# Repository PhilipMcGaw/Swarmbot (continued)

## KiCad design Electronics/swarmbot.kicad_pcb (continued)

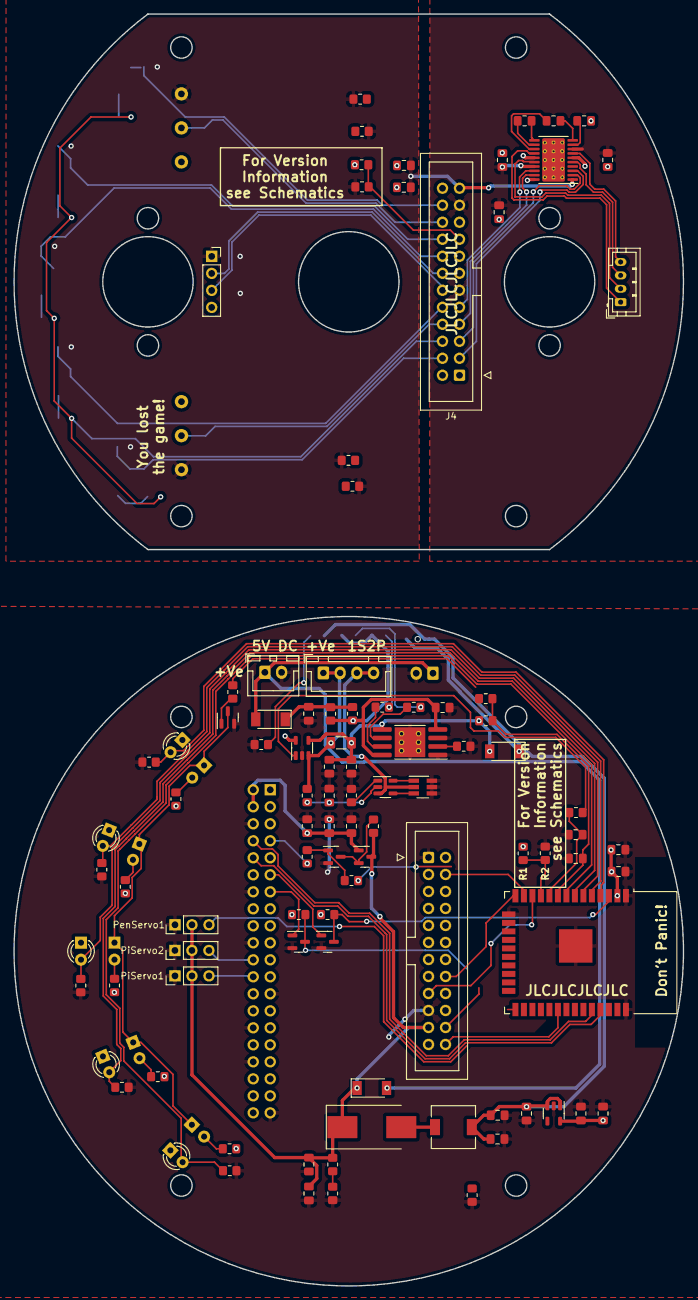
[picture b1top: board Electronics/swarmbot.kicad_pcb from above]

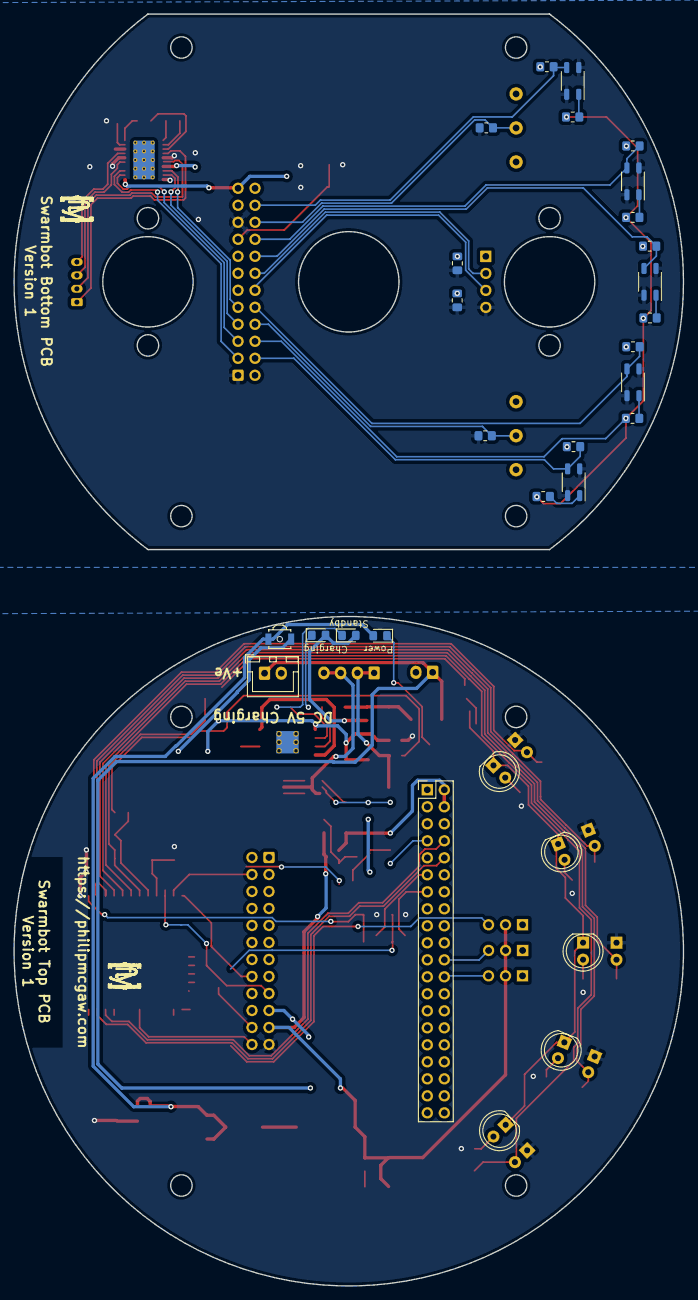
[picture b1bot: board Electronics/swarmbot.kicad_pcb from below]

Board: 2 copper layers, 100.0 x 190.0 mm, 131 parts (32 on the bottom side), 105 nets.

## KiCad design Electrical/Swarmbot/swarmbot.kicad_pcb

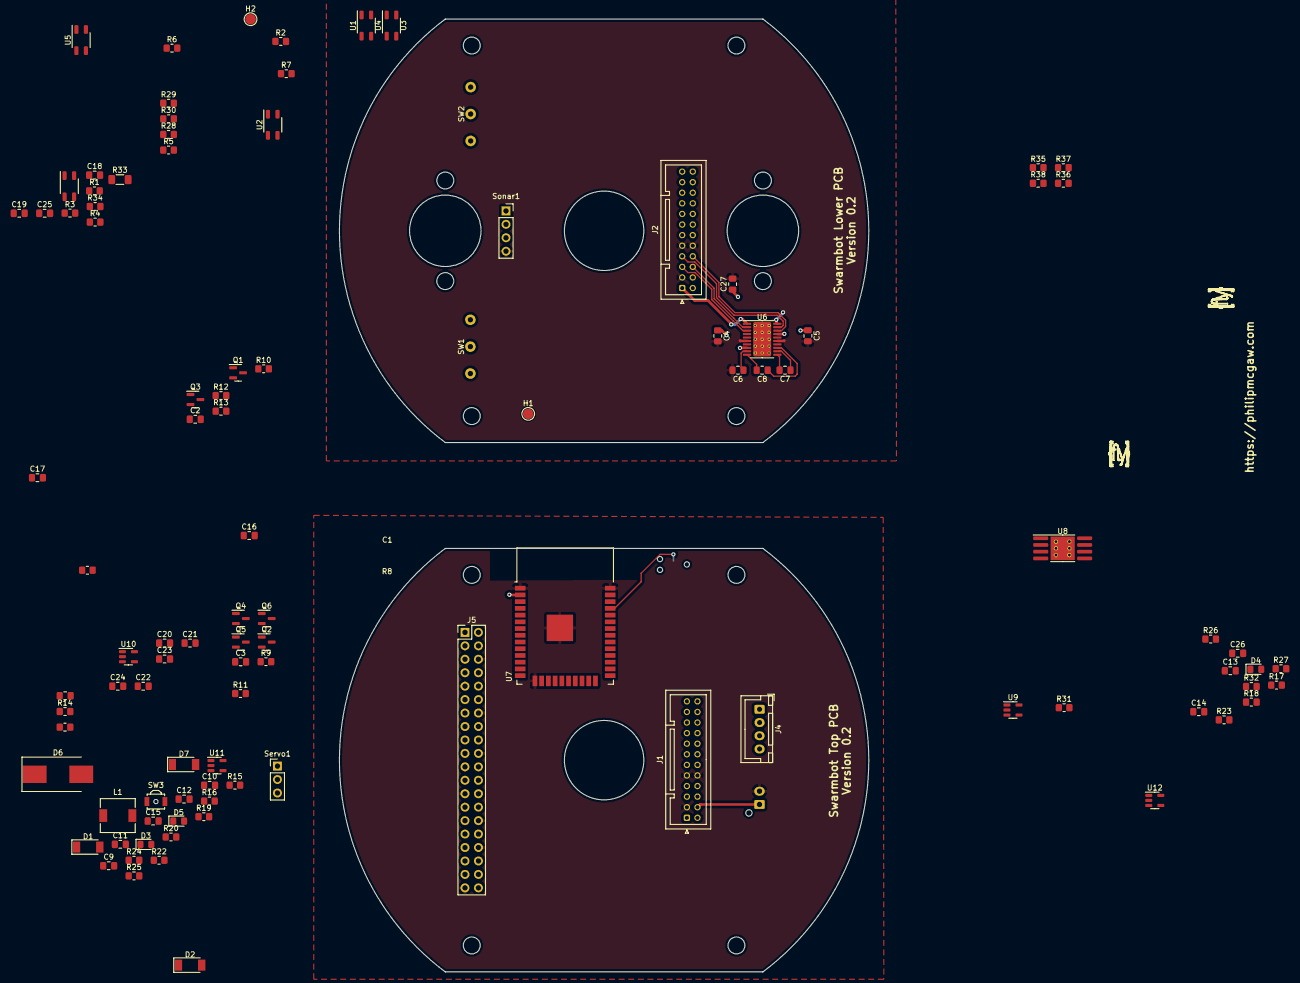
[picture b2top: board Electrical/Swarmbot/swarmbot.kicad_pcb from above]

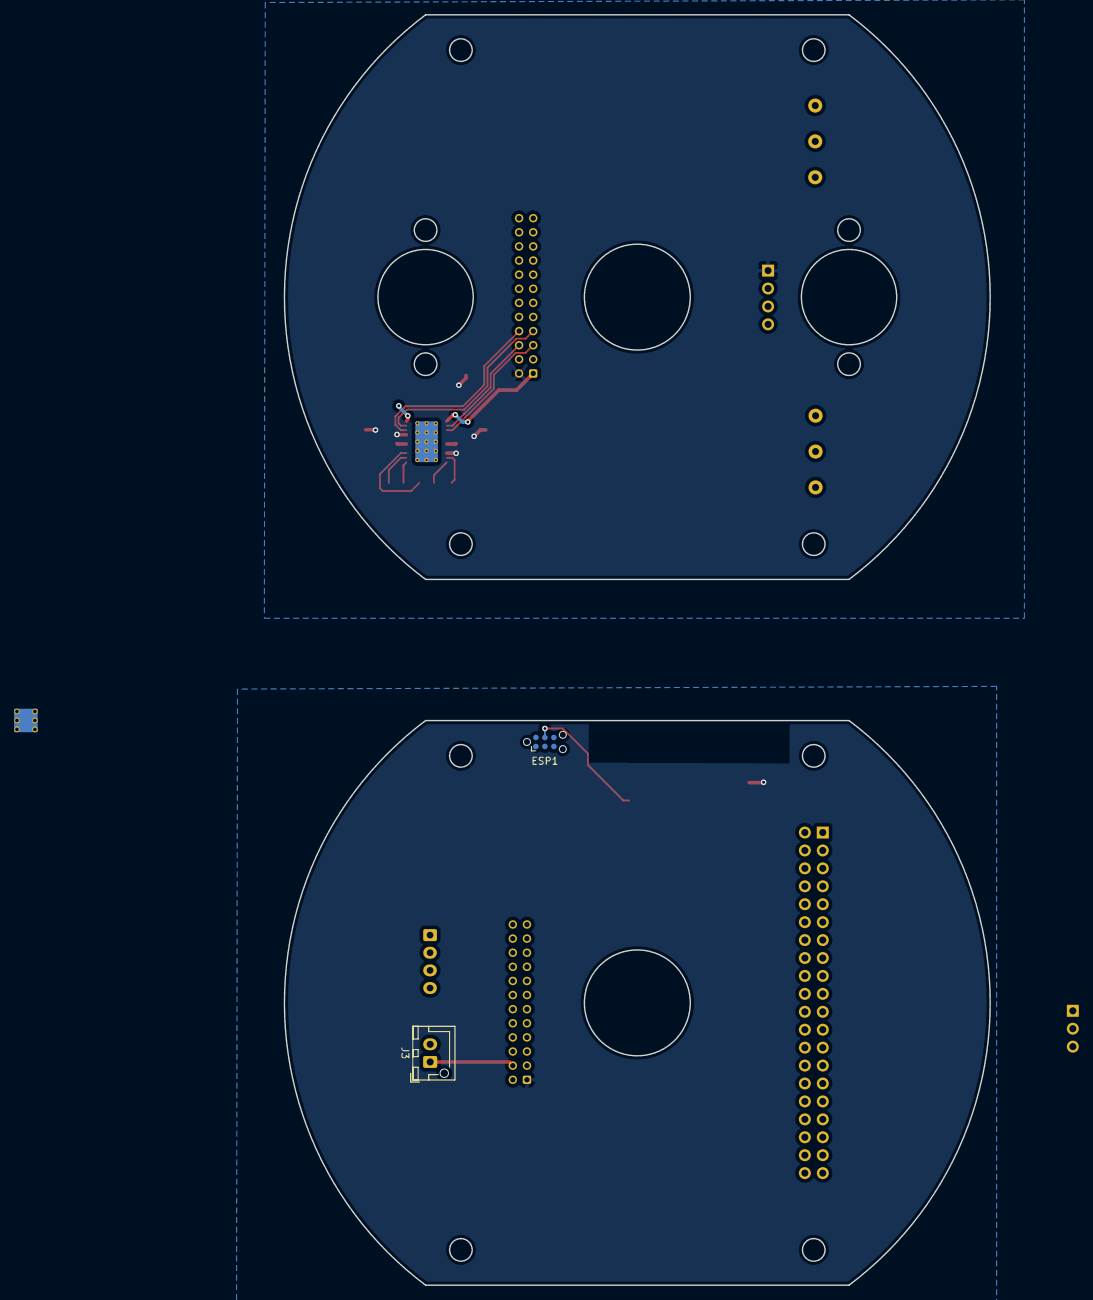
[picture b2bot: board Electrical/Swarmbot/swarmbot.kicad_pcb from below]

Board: 2 copper layers, 100.0 x 180.0 mm, 106 parts (2 on the bottom side), 84 nets.

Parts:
C1, C2, C9, C10, C11, C13, C14, C17, C22, C25: 10uF; C_0805_2012Metric_Pad1.18x1.45mm_HandSolder
C3, C4, C5, C6, C7, C8, C12, C26, C27: 100pF; C_0805_2012Metric_Pad1.18x1.45mm_HandSolder
C15, C16, C19, C20: 22uF; C_0805_2012Metric_Pad1.18x1.45mm_HandSolder
C18, C24: 100nF; C_0805_2012Metric_Pad1.18x1.45mm_HandSolder
C21, C23: 1uF; C_0805_2012Metric_Pad1.18x1.45mm_HandSolder
D1, D2, D7: RBR3LAM30BTFTR; D_SOD-128
D3: Power; LED_0805_2012Metric_Pad1.15x1.40mm_HandSolder
D4: Charging; LED_0805_2012Metric_Pad1.15x1.40mm_HandSolder
D5: Standby; LED_0805_2012Metric_Pad1.15x1.40mm_HandSolder
D6: SS54; D_SMC_Handsoldering
ESP1: ESP Programming TagConnect; Tag-Connect_TC2030-IDC-NL_2x03_P1.27mm_Vertical
H1: +VE; TestPoint_Pad_D2.0mm
H2: -VE; TestPoint_Pad_D2.0mm
J1, J2: 12x2 JST; JST_PUD_B24B-PUDSS_2x12_P2.00mm_Vertical
J3: Charging Header; JST_XH_B2B-XH-AM_1x02_P2.50mm_Vertical
J4: Battery 1S2P; JST_XH_B4B-XH-A_1x04_P2.50mm_Vertical
J5: Raspberry_Pi_2_3; PinHeader_2x20_P2.54mm_Vertical
L1: 3.3uH; L_6.3x6.3_H3
Logo1, Logo2: SquashedFlyLogo; SquashedFlySilk
Q1, Q2, Q3, Q4: BSH108; SOT-23
Q5, Q6: RSC002P03; SOT-23
R1, R2, R8, R9, R10, R11, R12, R13, R14, R15, R16, R17, R18, R19, R20, R21, R30, R37, R38: 10k; R_0805_2012Metric_Pad1.20x1.40mm_HandSolder
R3, R4, R5, R6, R7, R35, R36: 470; R_0805_2012Metric_Pad1.20x1.40mm_HandSolder
R22, R25, R26: 1k; R_0805_2012Metric_Pad1.20x1.40mm_HandSolder
R23, R24: 2R; R_0805_2012Metric_Pad1.20x1.40mm_HandSolder
R27: 30k; R_0805_2012Metric_Pad1.20x1.40mm_HandSolder
R28: 1k2; R_0805_2012Metric_Pad1.20x1.40mm_HandSolder
R29: 73k; R_0805_2012Metric_Pad1.20x1.40mm_HandSolder
R31, R34: 2k7; R_0805_2012Metric_Pad1.20x1.40mm_HandSolder
R32: 330; R_0805_2012Metric_Pad1.20x1.40mm_HandSolder
R33: .0025R; R_1206_3216Metric_Pad1.30x1.75mm_HandSolder
SW1: Left; TypeD
SW2: Right; TypeC
SW3: SW_SPST; SW_SPST_B3U-3000P-B
Servo1: Conn_01x03_Male; PinHeader_1x03_P2.54mm_Vertical
Sonar1: Conn_01x04_Male; PinSocket_1x04_P2.54mm_Vertical
U1, U2, U3, U4, U5: QRE1113GR; OnSemi_CASE100CY
U6: MPC17531A; HTSSOP-20-1EP_4.4x6.5mm_P0.65mm_EP3.4x6.5mm_Mask2.75x3.43mm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
U7: ESP32-WROOM-32D; ESP32-WROOM-32
U8: TP4056; SOP-8-1EP_4.57x4.57mm_P1.27mm_EP4.57x4.45mm_ThermalVias
U9, U11: AP2112K-3.3; SOT-23-5
U10: AP9101CK; SOT-23-5
U12: INA138; SOT-23-5

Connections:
+3V3: C11.1, C12.1, C22.1, C23.1, ESP1.1 (VCC), J1.1, R16.1, R17.1, U7.2 (VDD), U9.5 (VOUT), U11.5 (VOUT), U12.5 (V+)
+5V: C19.1, C20.1, D6.1 (K), D7.1 (K), J1.2, Q5.3 (D), Q6.3 (D), R18.1, R19.1, R29.2, Servo1.2
+BATT: C17.1, C18.1, D1.2 (A), R20.2, R32.2, R33.2, U8.5 (BAT), U12.3 (+)
/Charging Pad Lower: H1.1, J2.4
/Charging Top Pad: D2.2 (A), D7.2 (A), J1.4, J3.1
/H-Bridge 1A Lower: J2.6, U6.2 (IN1A)
/H-Bridge 1A Top: J1.8, U7.8 (IO32)
/H-Bridge 1B Lower: J2.5, U6.3 (IN1B)
/H-Bridge 1B Top: J1.5, U7.9 (IO33)
/H-Bridge 2A Lower: J2.7, U6.19 (IN2A)
/H-Bridge 2A Top: J1.7, U7.7 (IO35)
/H-Bridge 2B Lower: J2.8, U6.18 (IN2B)
/H-Bridge 2B Top: J1.6, U7.6 (IO34)
/Left Switch Lower: J2.15, R1.1, SW1.2 (n/o)
/Left Switch Top: J1.15, U7.14 (IO12)
/Line Sensor 1 Lower: J2.17, R8.2, U1.3
/Line Sensor 1 Top: J1.17, U7.16 (IO13)
/Line Sensor 2 Lower: J2.19, R9.2, U2.3
/Line Sensor 2 Top: J1.19, U7.23 (IO15)
/Line Sensor 3 Lower: J2.11, R10.2, U3.3
/Line Sensor 3 Top: J1.11, U7.24 (IO2)
/Line Sensor 4 Lower: J2.21, R11.2, U4.3
/Line Sensor 4 Top: J1.21, U7.27 (IO16)
/Line Sensor 5 Lower: J2.18, R12.2, U5.3
/Line Sensor LEDs Lower: J2.16, R3.1, R4.1, R5.1, R6.1, R7.1
/Line Sensor LEDs Top: C10.1, J1.16, Q6.1 (S)
/Lower PCB 3V3: C1.1, C2.1, J2.1, R8.1, R9.1, R10.1, R11.1, R12.1, R35.1, R36.1, R37.1, R38.1, SW1.1 (c), SW2.1 (c), U6.1 (VDD)
/Lower PCB 5V: C3.1, C4.1, C5.1, C27.1, J2.2, Sonar1.1, U6.8 (VM1), U6.17 (VM2)
/Lower PCB GND: C1.2, C2.2, C3.2, C4.2, C5.2, C6.2, C27.2, H2.1, J2.3, J2.9, J2.10, R1.2, R2.2, Sonar1.4, U1.2 (K), U1.4, U2.2 (K), U2.4, U3.2 (K), U3.4, U4.2 (K), U4.4, U5.2 (K), U5.4, U6.6 (PGND1), U6.15 (PGND2), U6.20 (LGND)
/Motor Sensor 1 Lower: J2.13, R37.2
/Motor Sensor 1 Top: J1.13, U7.33 (IO21)
/Motor Sensor 2 Lower: J2.14, R38.2
/Motor Sensor 2 Top: J1.14, U7.36 (IO22)
/Right Switch Lower: J2.20, R2.1, SW2.2 (n/o)
/Right Switch Top: J1.20, U7.13 (IO14)
/Sonar Echo Lower: J2.22, Sonar1.3
/Sonar Echo Top: J1.22, U7.12 (IO27)
/Sonar Trigger Lower: J2.23, Sonar1.2
/Sonar Trigger Top: J1.23, U7.11 (IO26)
/Top PCB/ESP32/5V Switch 1: R14.1, U7.28 (IO17)
/Top PCB/ESP32/5V Switch Aux: J5.7 (GCLK0/GPIO4), R13.1
/Top PCB/ESP32/5V Switched 1: C9.1, C25.1, C26.1, J5.2 (5V), J5.4 (5V), Q5.1 (S)
/Top PCB/ESP32/Bat I: C24.1, R34.1, U7.37 (IO23)
/Top PCB/ESP32/Bat V: C13.1, R20.1, R21.2, U7.10 (IO25)
/Top PCB/ESP32/Flash: ESP1.6 (SWO), J5.16 (GPIO23), Q1.1 (G)
/Top PCB/ESP32/Line Sensor LED: R15.1, U7.26 (IO4)
/Top PCB/ESP32/Pen Servo: Servo1.3, U7.29 (IO5)
/Top PCB/ESP32/RX: ESP1.2 (SWDIO), J5.8 (GPIO14/TXD), U7.34 (RXD0/IO3)
/Top PCB/ESP32/Reset: ESP1.3 (NRESET), J5.18 (GPIO24), Q2.1 (G)
/Top PCB/ESP32/TX: ESP1.4 (SWCLK), J5.10 (GPIO15/RXD), U7.35 (TXD0/IO1)
/Top PCB/ESP32/enable: Q2.3 (D), R17.2, U7.3 (EN)
/Top PCB/ESP32/program: Q1.3 (D), R16.2, U7.25 (IO0)
/Top PCB/Power/+BatDiode: D1.1 (K), SW3.2 (B)
/Top PCB/Power/Bat+VE: J4.1, J4.2, R33.1, U12.4 (-)
/Top PCB/Power/PowerInDiode: C14.1, D2.1 (K), R23.2, R24.2
/Top PCB/Power/PowerInInrush: D4.2 (A), D5.2 (A), R23.1, R24.1, U8.4 (VCC), U8.8 (CE)
/Top PCB/Power/VBAT: C15.1, C16.1, C21.1, D3.2 (A), L1.1, SW3.1 (A), U9.1 (VIN), U9.3 (EN), U11.1 (VIN), U11.3 (EN)
/Top PCB/Power/vbatInductor: D6.2 (A), L1.2
GND: C9.2, C10.2, C11.2, C12.2, C13.2, C14.2, C15.2, C16.2, C17.2, C18.2, C19.2, C20.2, C21.2, C22.2, C23.2, C24.2, C25.2, C26.2, ESP1.5 (GND), J1.3, J1.9, J1.10, J3.2, J5.6 (GND), J5.9 (GND), J5.14 (GND), J5.20 (GND), J5.25 (GND), J5.30 (GND), J5.34 (GND), J5.39 (GND), Q1.2 (S), Q2.2 (S), Q3.2 (S), Q4.2 (S), R21.1, R22.1, R27.1, R28.1, R30.1, R31.1, Servo1.1, U7.1 (GND), U7.15 (GND), U7.38 (GND), U7.39 (GND), U8.1 (TEMP), U8.3 (GND), U8.9, U9.2 (GND), U11.2 (GND), U12.2 (GND)
unnamed: C6.1, U6.9 (CRES)
unnamed: C7.1, U6.12 (C1L)
unnamed: C7.2, U6.11 (C1H)
unnamed: C8.1, U6.13 (C2L)
unnamed: C8.2, U6.10 (C2H)
unnamed: D3.1 (K), R22.2
unnamed: D4.1 (K), R25.2
unnamed: D5.1 (K), R26.1
unnamed: J4.3, J4.4
unnamed: Q3.1 (G), R13.2, R14.2
unnamed: Q3.3 (D), Q5.2 (G), R18.2
unnamed: Q4.1 (G), R15.2
unnamed: Q4.3 (D), Q6.2 (G), R19.2
unnamed: R3.2, U1.1 (A)
unnamed: R4.2, U2.1 (A)
unnamed: R5.2, U3.1 (A)
unnamed: R6.2, U4.1 (A)
unnamed: R7.2, U5.1 (A)
unnamed: R25.1, U8.7 (~CHRG)
unnamed: R26.2, U8.6 (~STDBY)
unnamed: R28.2, U8.2 (PROG)
unnamed: R29.1, R30.2
unnamed: R31.2, U10.1 (VM)
unnamed: R32.1, U10.2 (VDD)
unnamed: R34.2, U12.1

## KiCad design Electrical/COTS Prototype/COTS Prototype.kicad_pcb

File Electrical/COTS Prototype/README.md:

# KiCAD Blank Project

This is Philip McGaw's default blank project.

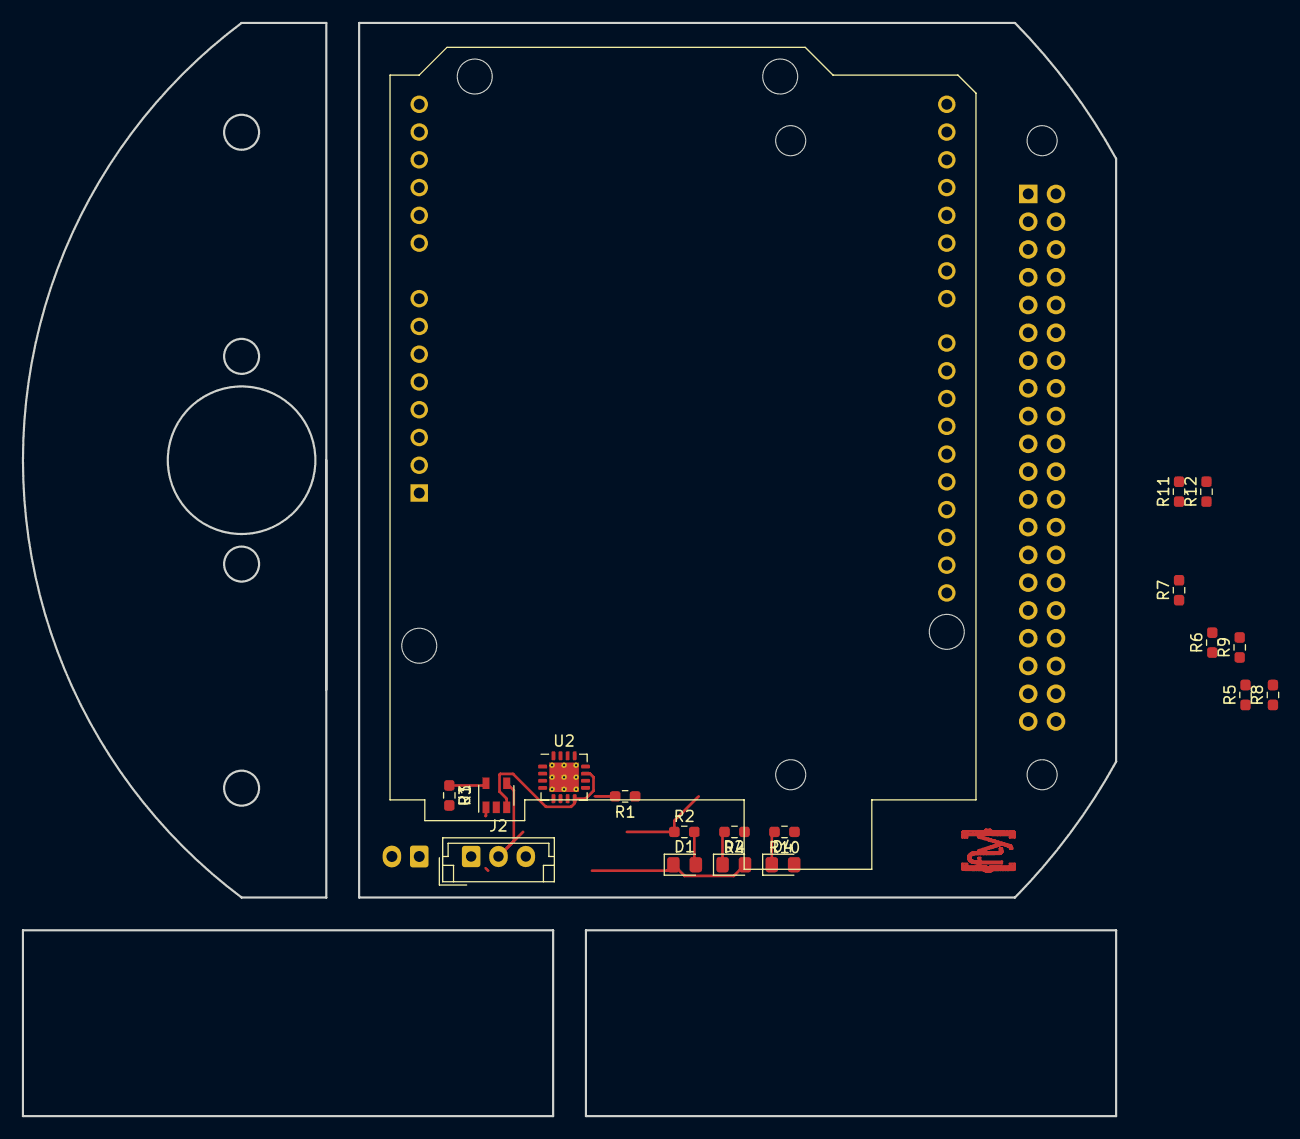
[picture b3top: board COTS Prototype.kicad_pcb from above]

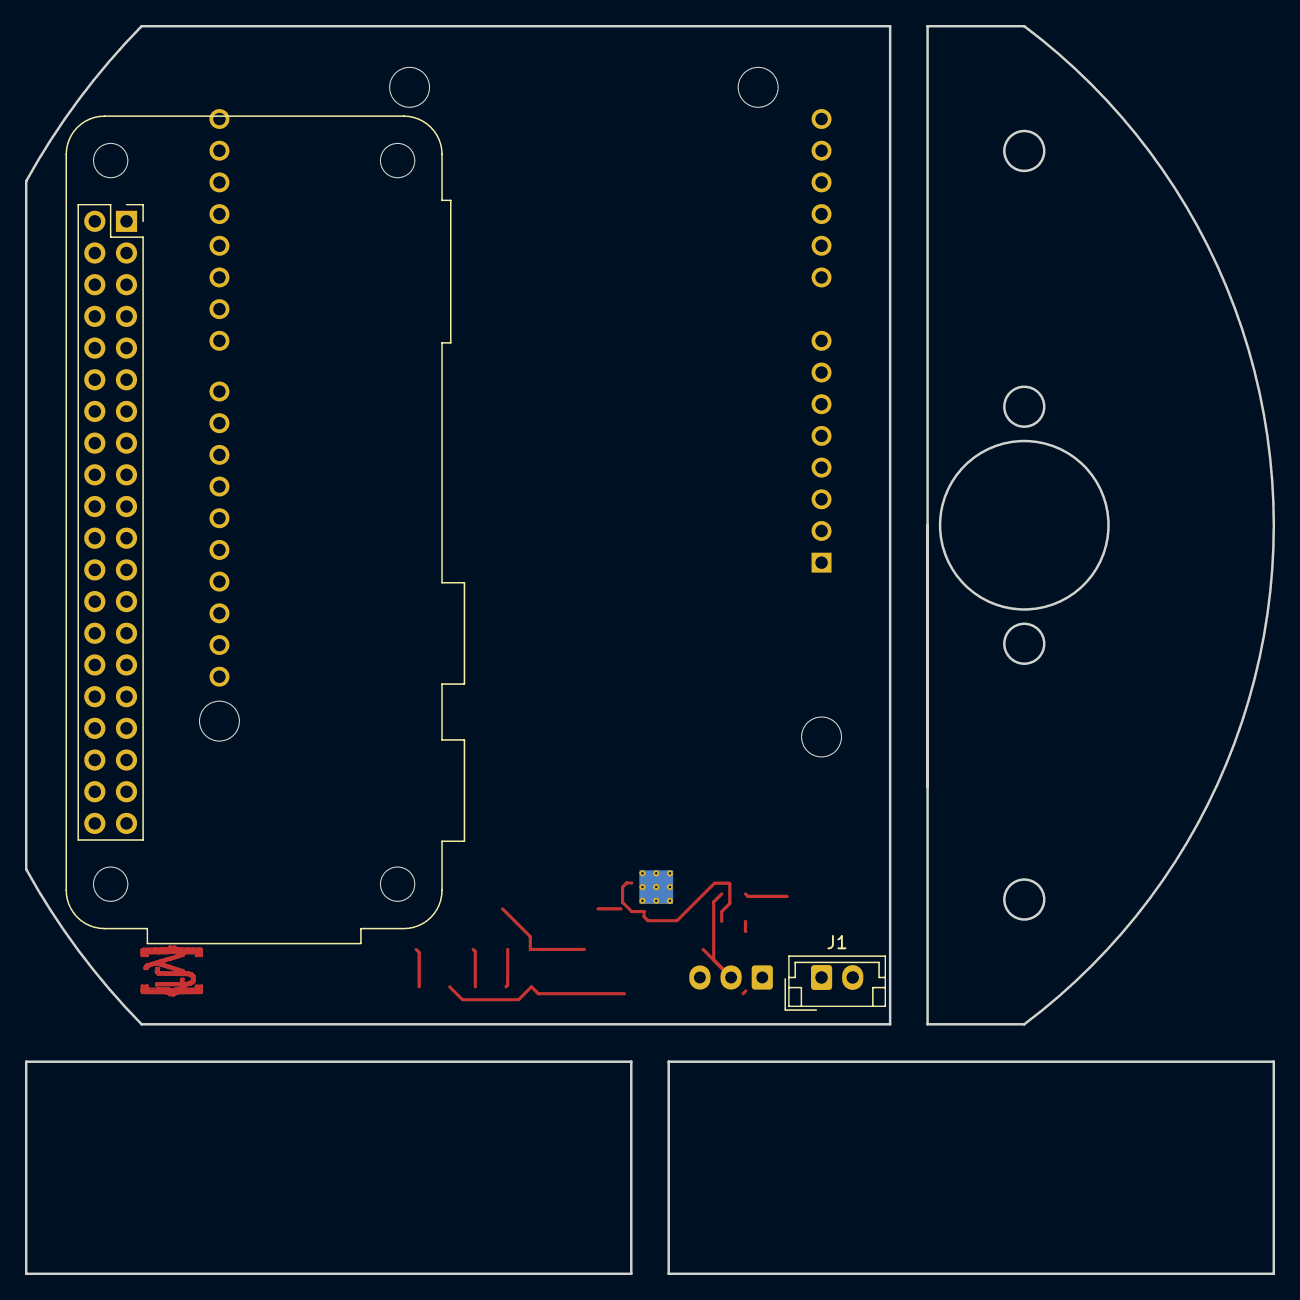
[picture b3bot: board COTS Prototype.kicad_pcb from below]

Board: 2 copper layers, 100.0 x 100.0 mm, 22 parts (2 on the bottom side), 17 nets.

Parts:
A1: Arduino_UNO_R3; Arduino_UNO_R3_WithMountingHoles
D1: Orange; LED_0805_2012Metric_Pad1.15x1.40mm_HandSolder
D2: Green; LED_0805_2012Metric_Pad1.15x1.40mm_HandSolder
D4: Blue; LED_0805_2012Metric_Pad1.15x1.40mm_HandSolder
J1: Battery; JST_EH_B2B-EH-A_1x02_P2.50mm_Vertical
J2: Charger; JST_EH_B3B-EH-A_1x03_P2.50mm_Vertical
J3: Raspberry_Pi_2_3; Raspberry_Pi_Zero_Socketed_THT_FaceDown_MountingHoles
Logo1: SquashedFlyLogo; SquashedFlyBrightCopper
R1, R5: 10k; R_0603_1608Metric_Pad0.98x0.95mm_HandSolder
R2: 470; R_0603_1608Metric_Pad0.98x0.95mm_HandSolder
R3: 2k; R_0603_1608Metric_Pad0.98x0.95mm_HandSolder
R4, R10: 1k; R_0603_1608Metric_Pad0.98x0.95mm_HandSolder
R6: 1M85; R_0603_1608Metric_Pad0.98x0.95mm_HandSolder
R7: 1M37; R_0603_1608Metric_Pad0.98x0.95mm_HandSolder
R8: 340k; R_0603_1608Metric_Pad0.98x0.95mm_HandSolder
R9: 200k; R_0603_1608Metric_Pad0.98x0.95mm_HandSolder
R11: 1k5; R_0603_1608Metric_Pad0.98x0.95mm_HandSolder
R12: 3k3; R_0603_1608Metric_Pad0.98x0.95mm_HandSolder
U1: MCP73831-2-OT; SOT-23-5
U2: TPS61090; Texas_S-PVQFN-N16_EP2.7x2.7mm_ThermalVias

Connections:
+5V: A1.5, D4.2, R6.1, U2.1, U2.15, U2.16
Bat_+Ve: R7.1, U1.3, U2.8, U2.11
GND: A1.6, A1.7, A1.29, J1.2, J2.1, J2.3, J3.6, J3.9, J3.14, J3.20, J3.25, J3.30, J3.34, J3.39, R3.2, R4.1, R5.2, R8.2, R9.2, R10.1, R12.2, U1.2, U2.5, U2.6, U2.7, U2.10, U2.13, U2.17
unnamed: D1.1, D2.2, U1.1
unnamed: D1.2, R2.2
unnamed: D2.1, R4.2
unnamed: D4.1, R10.2
unnamed: U2.3, U2.4
unnamed: R3.1, U1.5
unnamed: R6.2, R9.1, U2.14
unnamed: R7.2, R8.1, U2.9
On_Charge?: A1.28, R1.1
RPi_RX: J3.10, R11.2, R12.1
RPi_Supply: J3.2, J3.4
RPi_to_uC: A1.15, J3.8
Supply_+Ve: J2.2, R1.2, R2.1, R5.1, U1.4
uC_TX: A1.16, R11.1

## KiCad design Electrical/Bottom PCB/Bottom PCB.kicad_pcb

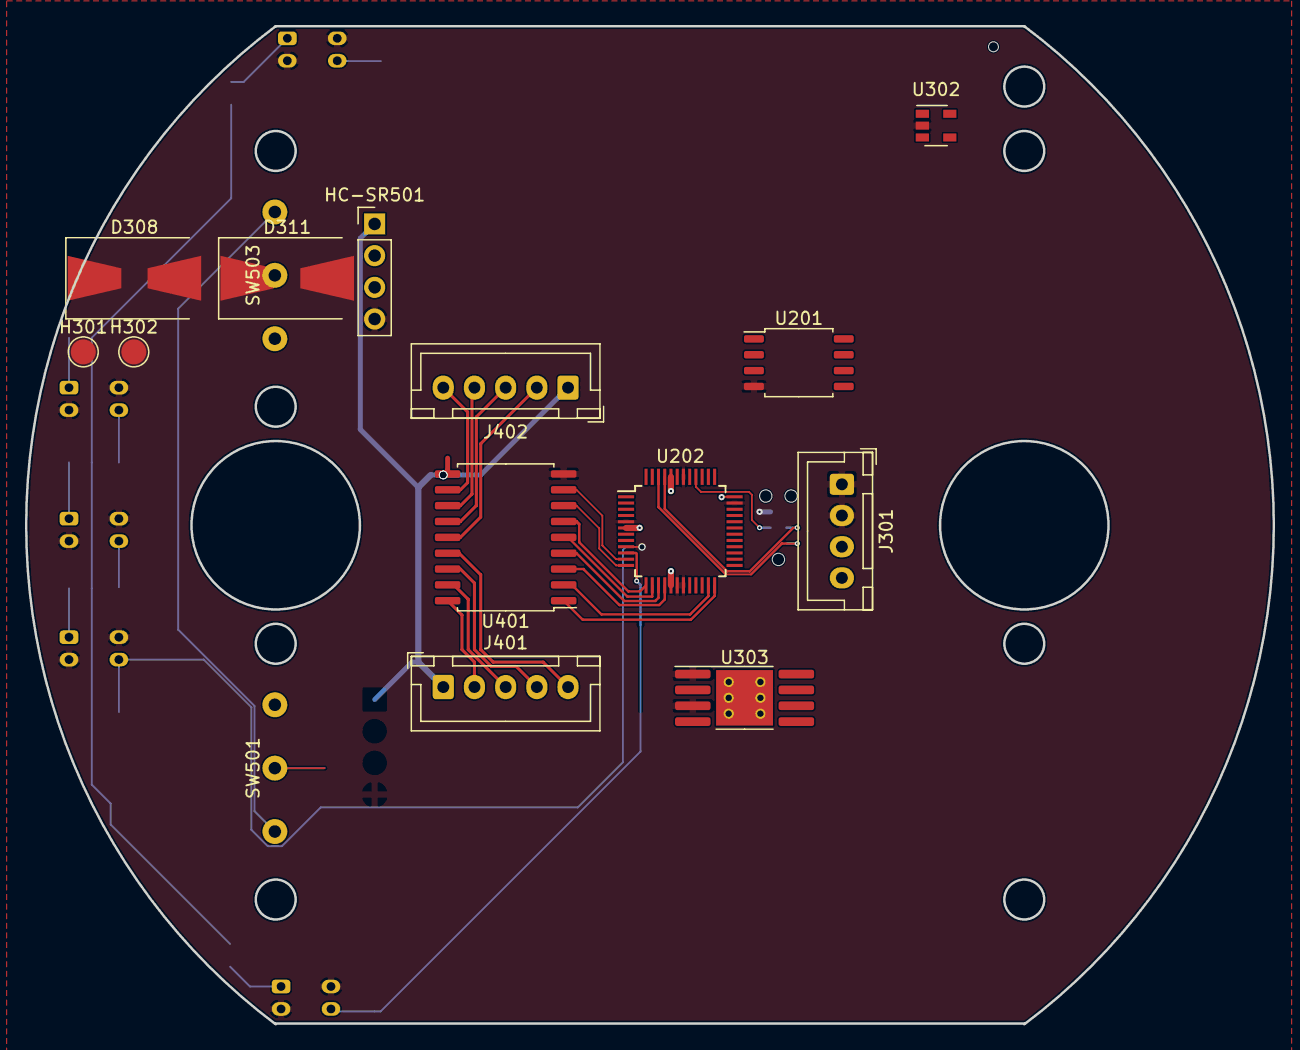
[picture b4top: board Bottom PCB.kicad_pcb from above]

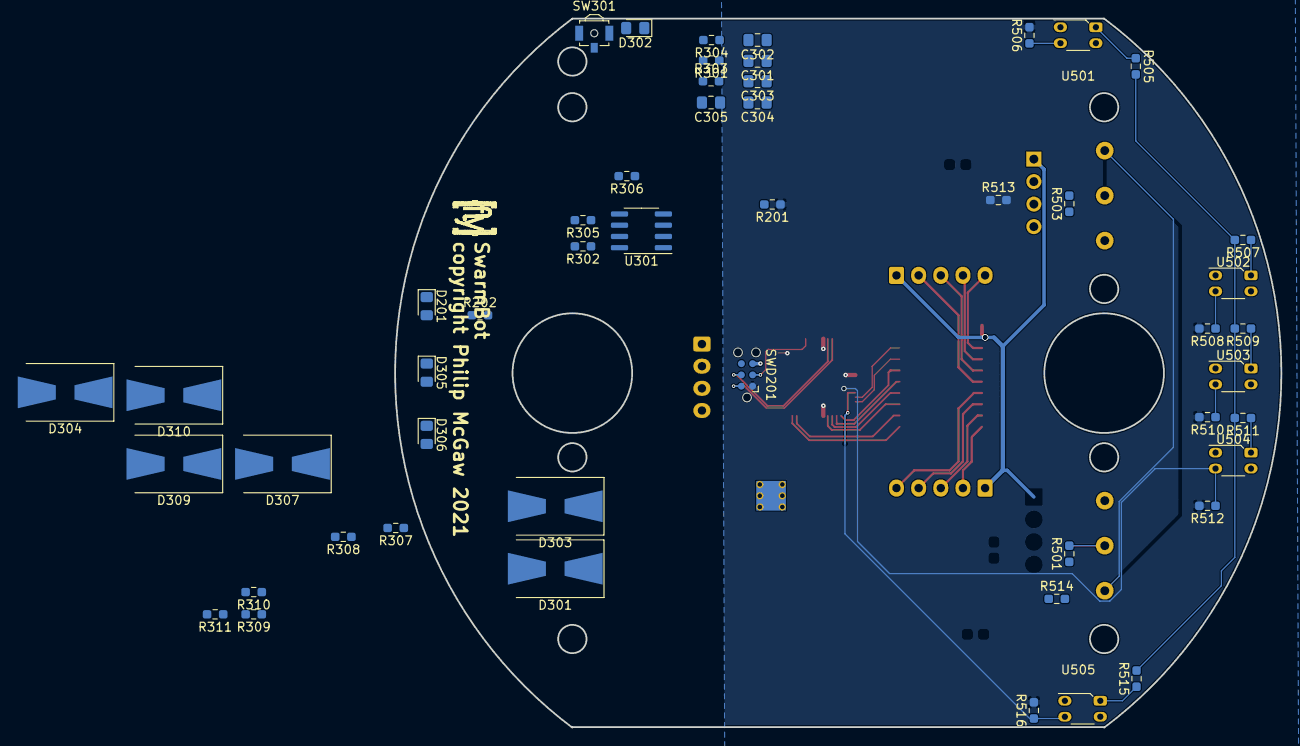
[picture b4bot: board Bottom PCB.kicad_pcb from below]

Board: 2 copper layers, 100.0 x 80.0 mm, 66 parts (51 on the bottom side), 59 nets.

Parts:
C301, C302, C303, C304: 22uF; C_0805_2012Metric_Pad1.15x1.40mm_HandSolder
C305: 10uF; C_0805_2012Metric_Pad1.15x1.40mm_HandSolder
D201: LED; LED_0805_2012Metric_Pad1.15x1.40mm_HandSolder
D301, D303, D304, D307, D308, D309, D310, D311: SS24; D_SMB-SMC_Universal_Handsoldering
D302: Power; LED_0805_2012Metric_Pad1.15x1.40mm_HandSolder
D305: Charging; LED_0805_2012Metric_Pad1.15x1.40mm_HandSolder
D306: Standby; LED_0805_2012Metric_Pad1.15x1.40mm_HandSolder
H301: +VE; TestPoint_Pad_D2.0mm
H302: -Ve; TestPoint_Pad_D2.0mm
HC-SR501: HC-SR04; PinHeader_1x04_P2.54mm_Vertical
J301: Battery 1S2P; JST_XH_B4B-XH-A_1x04_P2.50mm_Vertical
J401: Steper1; JST_XH_B5B-XH-A_1x05_P2.50mm_Vertical
J402: Steper2; JST_XH_B5B-XH-A_1x05_P2.50mm_Vertical
Logo101: SquashedFlyLogo; SquashedFly Logo
R201, R303, R306, R501, R503, R506, R508, R510, R512, R516: 10k; R_0603_1608Metric_Pad0.98x0.95mm_HandSolder
R202, R309, R310: 1k; R_0603_1608Metric_Pad0.98x0.95mm_HandSolder
R301: 47k; R_0603_1608Metric_Pad0.98x0.95mm_HandSolder
R302: 73k; R_0603_1608Metric_Pad0.98x0.95mm_HandSolder
R304: 470; R_0603_1608Metric_Pad0.98x0.95mm_HandSolder
R305: 30k; R_0603_1608Metric_Pad0.98x0.95mm_HandSolder
R307, R308: 2R; R_0603_1608Metric_Pad0.98x0.95mm_HandSolder
R311: 1k2; R_0603_1608Metric_Pad0.98x0.95mm_HandSolder
R505, R507, R509, R511, R515: 100; R_0603_1608Metric_Pad0.98x0.95mm_HandSolder
R513: 2k7; R_0603_1608Metric_Pad0.98x0.95mm_HandSolder
R514: 4k7; R_0603_1608Metric_Pad0.98x0.95mm_HandSolder
SW301: SW_SPST; SW_SPST_B3U-3100P-B
SW501: FL; TypeD
SW503: FR; TypeC
SWD201: Tag-Connect SWD; Tag-Connect_TC2030-IDC-NL_2x03_P1.27mm_Vertical
U201: GD25Q64C; SOIC-8_5.23x5.23mm_P1.27mm
U202: ATSAMD21G18A-AUT; TQFP-48_7x7mm_P0.5mm
U301: FP6298; SOIC-8_3.9x4.9mm_P1.27mm
U302: AP2112K-3.3; SOT-23-5
U303: TP4056; SOP-8-1EP_4.57x4.57mm_P1.27mm_EP4.57x4.45mm_ThermalVias
U401: ULN2003A; SOIC-18W_7.5x11.6mm_P1.27mm
U501, U502, U503, U504, U505: QRE1113; OnSemi_CASE100AQ

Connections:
+3V3: R201.1, R506.2, R508.2, R510.2, R512.2, R516.2, SWD201.1, U201.3, U201.7, U201.8, U202.6, U202.17, U202.36, U202.44, U302.5
+5V: C303.1, C304.1, D301.1, D303.1, HC-SR501.1, J401.1, J402.1, R302.2, U401.10
+BATT: C301.1, C302.1, D302.2, D307.1, D308.1, R301.2, SW301.2, U301.3, U301.4, U302.1, U302.3
A0: C305.1, R301.1, R303.2, U202.47
A1: R506.1, U202.3, U501.3
A2: R508.1, U202.7, U502.3
A3: R510.1, U202.8, U503.3
A4: R512.1, U202.9, U504.3
A5: R516.1, U202.10, U505.3
Charge: D304.2, D307.2, D308.2, D311.2, H301.1
D13: R202.2, U202.26
FLASH_CS: R201.2, U201.1, U202.39
FLASH_MISO: U201.2, U202.48
FLASH_MOSI: U201.5, U202.37
FLASH_SCK: U201.6, U202.38
GND: C301.2, C302.2, C303.2, C304.2, C305.2, D201.1, H302.1, HC-SR501.4, J301.1, J301.2, R303.1, R304.1, R305.1, R306.1, R311.1, R501.1, R503.1, R514.2, SWD201.5, U201.4, U202.5, U202.18, U202.19, U202.35, U202.42, U301.1, U301.5, U302.2, U303.1, U303.3, U401.9, U501.2, U501.4, U502.2, U502.4, U503.2, U503.4, U504.2, U504.4, U505.2, U505.4
IR: R505.2, R507.2, R509.2, R511.2, R515.2, U202.25
MD0: U202.24, U401.1
MD1: U202.23, U401.2
MD2: U202.16, U401.3
MD3: U202.15, U401.4
MD4: U202.14, U401.5
MD5: U202.13, U401.6
MD6: U202.12, U401.7
MD7: U202.11, U401.8
unnamed: D304.1, D311.1, R307.2, R308.2
unnamed: D201.2, R202.1
unnamed: D301.2, D303.2, U301.8
unnamed: D302.1, R304.2
unnamed: D305.1, R309.2
unnamed: D305.2, D306.2, R307.1, R308.1, U303.4, U303.8
unnamed: D306.1, R310.1
unnamed: D309.1, D310.1, SW301.1
unnamed: HC-SR501.3, R513.2
unnamed: J401.2, U401.18
unnamed: J401.3, U401.17
unnamed: J401.4, U401.16
unnamed: J401.5, U401.15
unnamed: J402.2, U401.14
unnamed: J402.3, U401.13
unnamed: J402.4, U401.12
unnamed: J402.5, U401.11
unnamed: R302.1, R306.2, U301.6
unnamed: R309.1, U303.7
unnamed: R310.2, U303.6
unnamed: R311.2, U303.2
unnamed: R505.1, U501.1
unnamed: R507.1, U502.1
unnamed: R509.1, U503.1
unnamed: R511.1, U504.1
unnamed: R515.1, U505.1
PowerIn: D309.2, D310.2, J301.3, J301.4, U303.5
RESET: SWD201.3, U202.40
SWCLK: SWD201.4, U202.45
SWDIO: SWD201.2, U202.46
Sonar_Echo: R513.1, R514.1
SwFL: R501.2, SW501.2
SwFR: R503.2, SW503.2
Switches: SW501.1, SW503.1

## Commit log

2020-05-02 Oops
    I seem to have added some mac only files…
2020-05-02 Who knows
2020-05-02 All good fun
2020-05-02 .DS_Store banished!
2020-05-02 Morne updated
2020-05-02 Fixed the file format
2020-05-05 small update
2020-05-07 Update LICENSE.md
    some spelling errors etc
2020-05-07 Delete SwarmBot PBS.xlsx
    meh
2020-05-07 Changed IR sensors to allow for passive measurments
2020-05-07 Adding 9 DoF IMU
2020-05-08 Change MCU
    swap arduino to ESP32-Wroom
    https://www.mouser.co.uk/ProductDetail/Espressif/ESP32-WROVER/?qs=chTDxNqvsynCfB3ibKeA%252bA%3D%3D
    Mouser No: 356-ESP32-WROVER
2020-05-11 Add reset / reboot circuit for ESP32, modify readme to remove eagle constraint as eagle is no longer in use.
2020-05-11 Moved components to sub sheets
    Continued on from Bob's work, in so much that I moved some items to additional sheets, increesed the size of the main header to include a half battery tap, and the addition of jumpers so that the dev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
2020-05-11 Set up MCP23017
    Added the main parts of an MCP23017
2020-05-11 simplified the pcb,
    Removed the shift registers and moved functionality onto the 16 way IO expander, also removed the H-Bridge, may re-add a I2C duel h-bridge at a later date.
    Thinking about best way to drive the four servo headers, may use I2C controller for them as well, as then the timing maths is removed from the main micro
2020-05-11 moved some parts to 5V supply
2020-05-11 removed the servos at the moment
2020-05-13 Added power switch
    Some more modifications
2020-05-16 added more stuff
2020-05-17 changed from 1206 to 0805
2021-05-25 hello
2021-06-01 Made some exciting changes
2021-06-02 random changes
2021-06-02 changed , to tabs
2021-06-02 a lot of updates
2021-06-02 Moved comments and updated some spellings.
2021-06-02 Cleaned up examples in folders.
2021-06-02 removed a line
2021-06-02 fixed spellings, and changed web address of Philip's site
2021-06-03 Added Raspberry Pi Zero to the breadboard, and did some work on cleaning up the wires,
    this is not finished, and will need a little more work…
2021-06-03 added serial
2021-06-03 Housekeeping
2021-06-03 COTS idea…
2021-06-04 Some odd reason git was being odd
2021-06-04 See it was being odd
2021-06-07 working on schematics
2021-06-18 changed COTs PCB
2021-10-14 made some changes
2021-10-20 try to remove the kicad backups
2021-10-20 some little changes have been made
2021-10-20 off to do other things for a second
    ;
2021-10-27 updated the excel
2021-10-27 some pcb changes
2021-11-01 added bom
2021-11-01 del backups
2021-11-01 sort out the backups?
2021-11-26 some changes were made
2021-11-27 removed the backups
2021-11-27 slight changes to layout
2021-11-28 don't use the enable pingit statusgit status
    ;
2021-11-29 Fixed the enable pin being used
2021-11-30 Cleaning up the stupid error with the pinout
2021-12-22 Get Arduino to work
